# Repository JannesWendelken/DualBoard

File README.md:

# DualBoard

A budget-friendly DIY macroboard based on the ATtiny85.

---

## Overview

I came up with the idea for it when I was looking for a small 2-key keyboard for Geometry Dash, but the prices were just way too high. So, I decided to design my own! This project lets you create your very own custom macroboard for a fraction of the cost of pre-built options.

---

## Features

- **Budget-friendly:** Designed to keep costs low.
- **Compact:** Small, portable design.
- **Customizable:** Modify the design to fit your needs.
- **Based on ATtiny85:** A small but powerful microcontroller that’s perfect for this kind of project.

---

## Pictures

Here are some images of the project:

- PCB:  

- Layout:  

- Schematic:  

---

## How to Build

Here’s a quick guide to get you started with building your own **DualBoard**:

1. **Order the PCB:**  
   You can use services like JLCPCB or any other PCB manufacturer to get your custom PCB made.
   
2. **Program the ATtiny85:**  
   Use the Arduino IDE to program the ATtiny85. You’ll find all the necessary code in the repository.

3. **Solder the Components:**  
   Solder the components onto the PCB. You’ll need basic soldering skills, and I recommend using the 0603 package for components to keep things compact and affordable.

4. **Print or Buy a Case:**  
   You can 3D print the case (I have a design for you), or purchase one online. The case will help protect the components and give the board a nice finish.

5. **Assemble the Board:**  
   Once everything is soldered and the case is ready, assemble the board, plug it in, and you're done!

---

## Bill of Materials (BOM)

Here’s the list of components you’ll need:

- **2x 1k Resistors**  
- **2x 68Ω Resistors**  
- **1x 4.7µF Capacitor**  
- **1x ATtiny85**  
- **1x USB Micro-B Connector**  
- **1x LED**  

**Note:**  
I used 0603 package components to keep the project cost-effective. However, if you’re not comfortable with hand-soldering small parts, feel free to change the component sizes to something more manageable.

---

## Customization

Feel free to modify the design and code to suit your needs. The beauty of this DIY project is that you can adapt it to any specific use case you have in mind!

---

## License

This project is open-source and free to modify. Please see the [LICENSE](LICENSE) for more details.

---

## Support

If you have any questions or need help, feel free to open an issue in the GitHub repository, and I’ll do my best to assist you!

---

By following these steps, you’ll have a fully functional, budget-friendly, and custom macroboard. I hope you enjoy building your own **DualBoard**!

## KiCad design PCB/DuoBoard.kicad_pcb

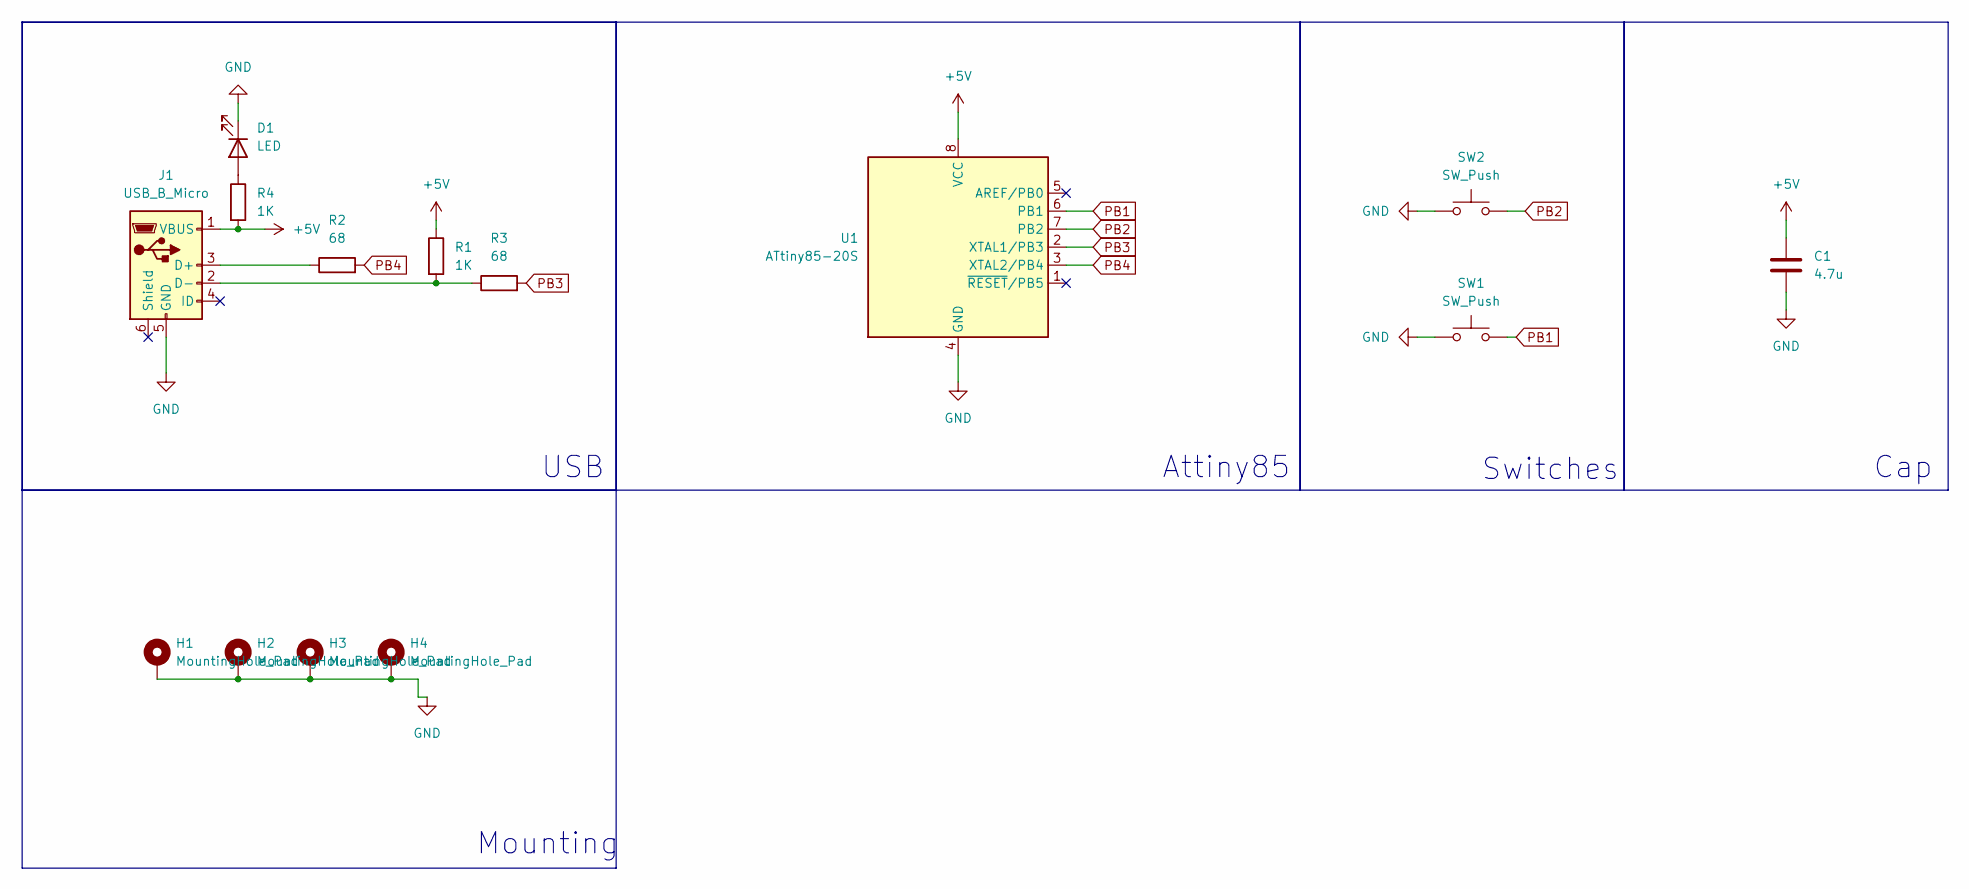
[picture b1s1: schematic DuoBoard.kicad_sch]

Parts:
C1: 4.7u; C_0201_0603Metric_Pad0.64x0.40mm_HandSolder
D1: LED; LED_0201_0603Metric_Pad0.64x0.40mm_HandSolder
H1, H2, H3, H4: MountingHole_Pad; MountingHole_2.2mm_M2_DIN965_Pad
J1: USB_B_Micro; USB_Micro-B_Molex-105017-0001
R1, R4: 1K; R_0201_0603Metric_Pad0.64x0.40mm_HandSolder
R2, R3: 68; R_0201_0603Metric_Pad0.64x0.40mm_HandSolder
SW1, SW2: SW_Push; SW_Cherry_MX_1.00u_PCB
U1: ATtiny85-20S; SOIC-8W_5.3x5.3mm_P1.27mm

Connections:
+5V: C1.1, J1.1 (VBUS), R1.1, R4.2, U1.8 (VCC)
GND: C1.2, D1.1 (K), H1.1, H2.1, H3.1, H4.1, J1.5 (GND), SW1.1, SW2.1, U1.4 (GND)
unnamed: D1.2 (A), R4.1
unnamed: J1.3 (D+), R2.1
unnamed: J1.2 (D-), R1.2, R3.1
PB1: SW1.2, U1.6 (PB1)
PB2: SW2.2, U1.7 (PB2)
PB3: R3.2, U1.2 (XTAL1/PB3)
PB4: R2.2, U1.3 (XTAL2/PB4)

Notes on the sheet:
USB
Attiny85
Switches
Cap
Mounting

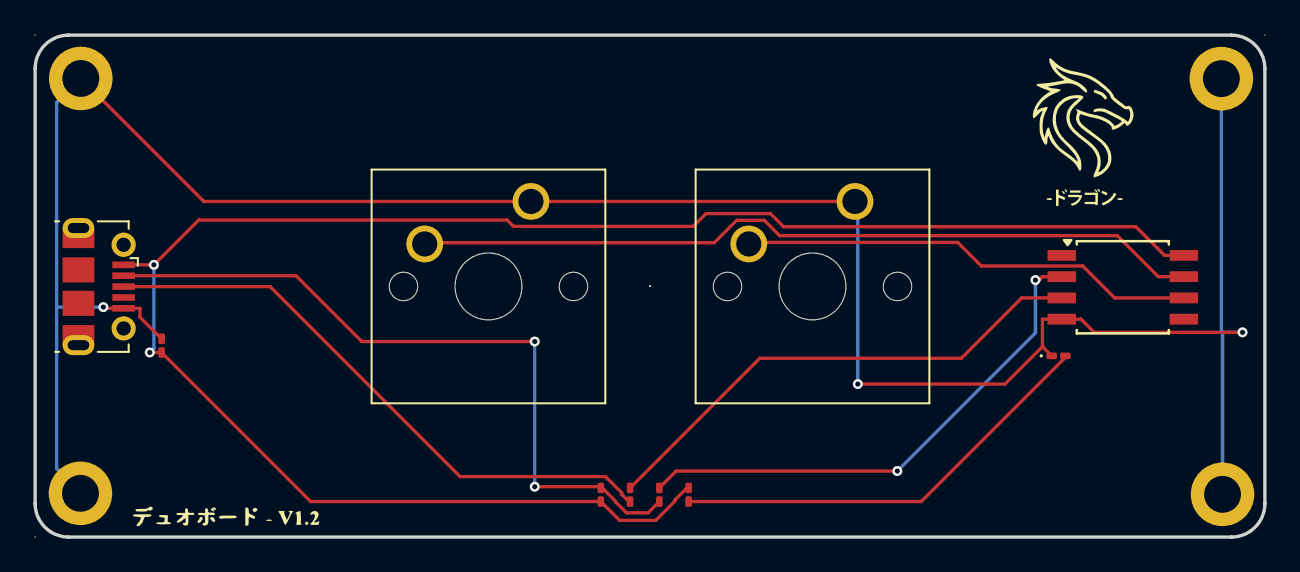
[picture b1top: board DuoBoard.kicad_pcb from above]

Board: 2 copper layers, 73.5 x 30.0 mm, 14 parts (0 on the bottom side), 9 nets.

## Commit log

2025-12-12 Rename DuoBoard.kicad_pro to PCB/DuoBoard.kicad_pro
2025-12-12 Rename Finished.png to IMG/finished.png
2025-12-12 Rename safasfasf.png to logo.png
2025-12-12 Rename Schematic.png to schematic.png
2025-12-12 Rename Layout.png to layout.png
